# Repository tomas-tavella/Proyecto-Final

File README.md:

# Proyecto-Final
Repositorio para todo lo que respecta al proyecto final de pilas de hidrogeno

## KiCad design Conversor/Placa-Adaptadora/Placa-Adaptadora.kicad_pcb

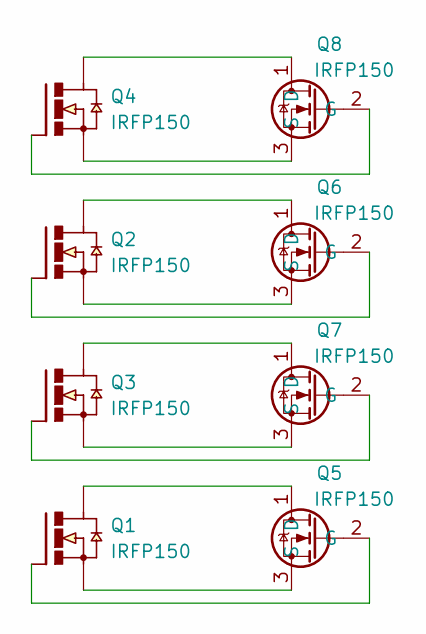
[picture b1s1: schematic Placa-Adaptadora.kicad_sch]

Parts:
Q1, Q2, Q3, Q4: IRFP150; TO247BV
Q5, Q6, Q7, Q8: IRFP150; TO-247-3_Vertical

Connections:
unnamed: Q2.D, Q6.1 (D)
unnamed: Q2.S, Q6.3 (S)
unnamed: Q4.D, Q8.1 (D)
unnamed: Q4.S, Q8.3 (S)
unnamed: Q1.D, Q5.1 (D)
unnamed: Q1.G, Q5.2 (G)
unnamed: Q1.S, Q5.3 (S)
unnamed: Q2.G, Q6.2 (G)
unnamed: Q3.D, Q7.1 (D)
unnamed: Q3.G, Q7.2 (G)
unnamed: Q3.S, Q7.3 (S)
unnamed: Q4.G, Q8.2 (G)

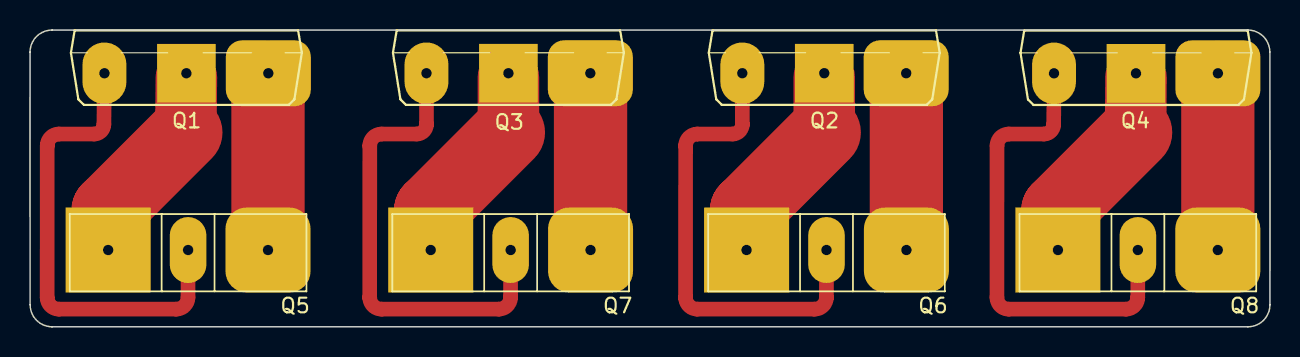
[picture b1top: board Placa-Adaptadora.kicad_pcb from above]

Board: 2 copper layers, 84.6 x 20.2 mm, 8 parts (0 on the bottom side), 12 nets.

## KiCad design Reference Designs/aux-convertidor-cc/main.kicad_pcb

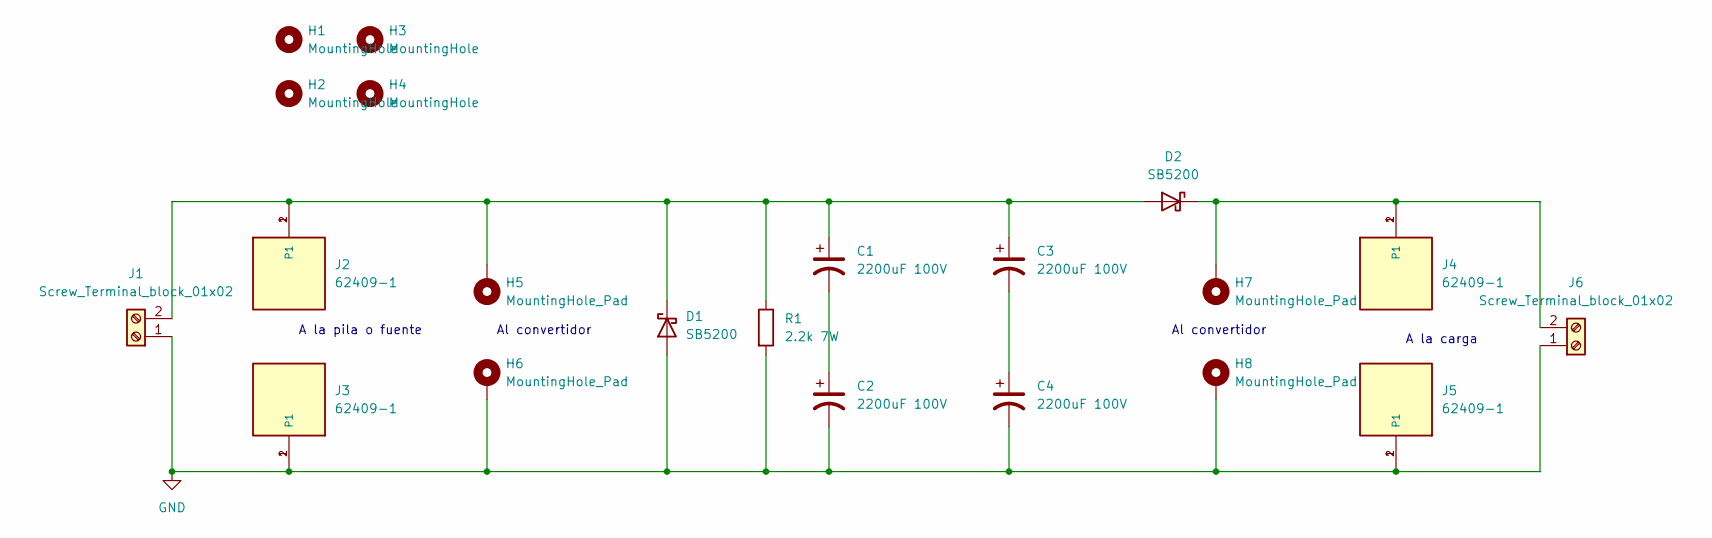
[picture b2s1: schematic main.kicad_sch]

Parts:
C1, C2, C3, C4: 2200uF 100V; CP_Radial_D25.0mm_P10.00mm_SnapIn
D1, D2: SB5200; D_DO-27_P15.24mm_Horizontal
H1, H2, H3, H4: MountingHole; MountingHole_3.2mm_M3
H5, H6, H7, H8: MountingHole_Pad; MountingHole_3.2mm_M3_Pad
J1, J6: Screw_Terminal_block_01x02; Degson_Screw_Terminal_block_01x02
J2, J3, J4, J5: 62409-1; TE_62409-1
R1: 2.2k 7W; R_Axial_Power_L38.0mm_W9.0mm_P40.64mm

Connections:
GND: C2.2, C4.2, D1.2 (A), H6.1, H8.1, J1.1, J3.1, J3.2 (P1), J5.1, J5.2 (P1), J6.1, R1.2
unnamed: C1.1, C3.1, D1.1 (K), D2.2 (A), H5.1, J1.2, J2.1, J2.2 (P1), R1.1
unnamed: C1.2, C2.1
unnamed: C3.2, C4.1
unnamed: D2.1 (K), H7.1, J4.1, J4.2 (P1), J6.2

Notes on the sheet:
Al convertidor
A la pila o fuente
A la carga

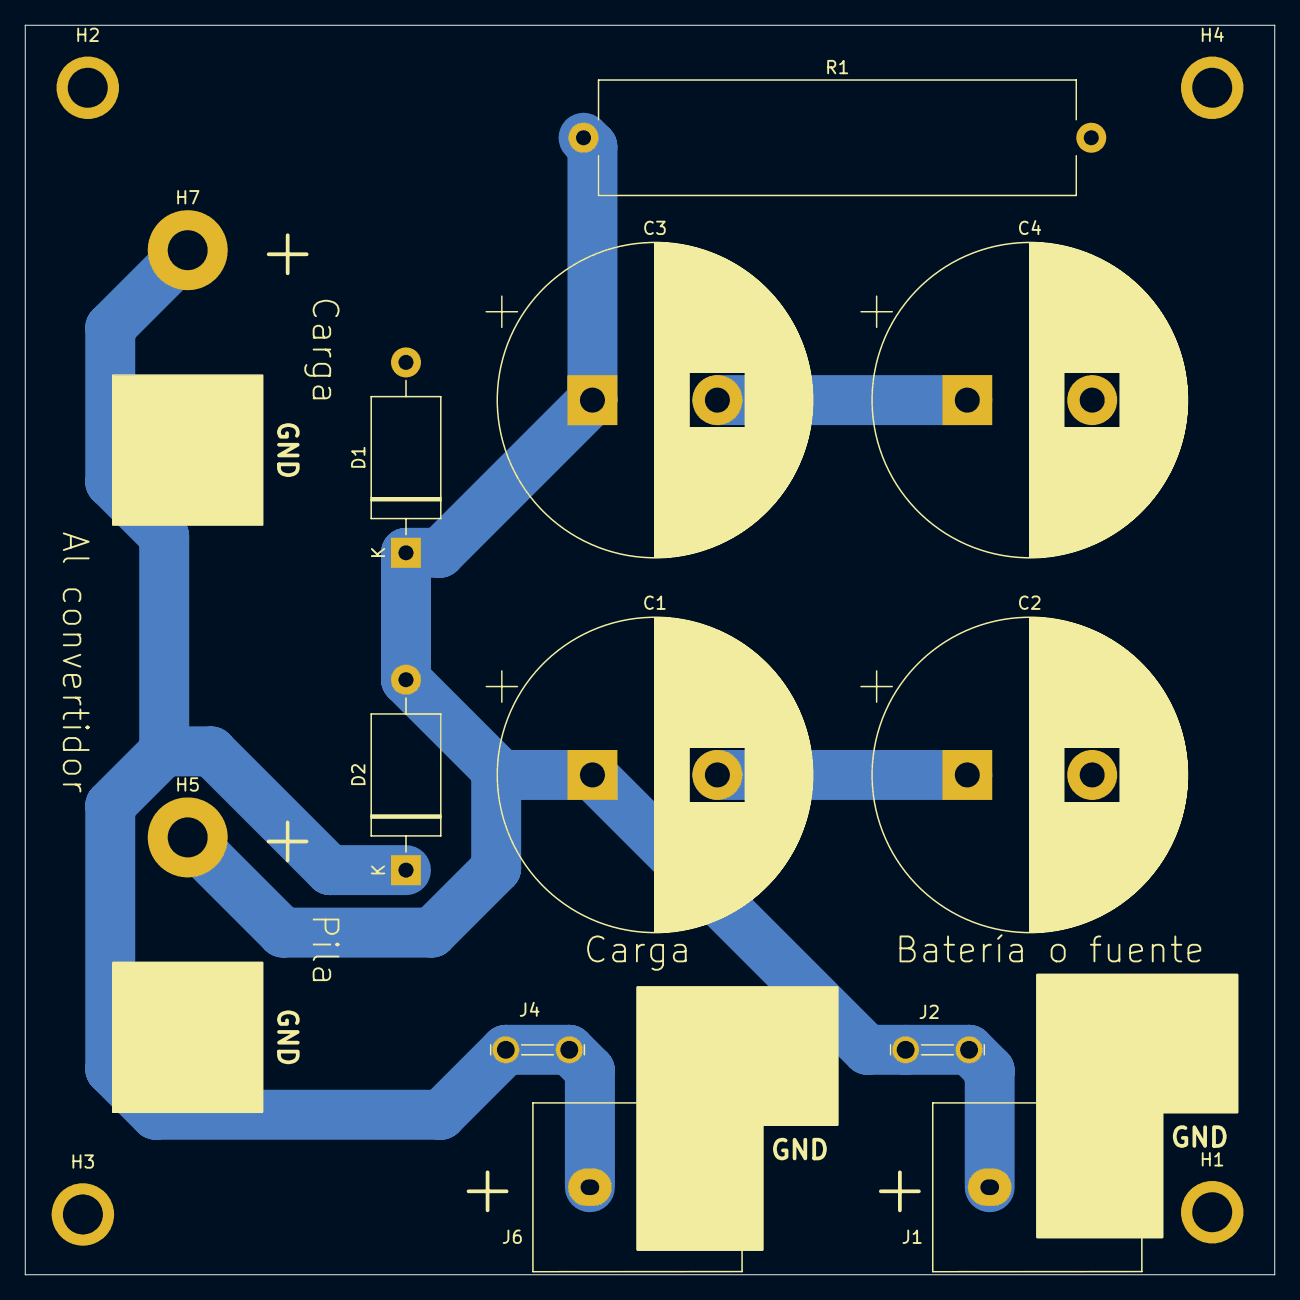
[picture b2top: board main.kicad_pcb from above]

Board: 2 copper layers, 100.0 x 100.0 mm, 21 parts (0 on the bottom side), 5 nets.

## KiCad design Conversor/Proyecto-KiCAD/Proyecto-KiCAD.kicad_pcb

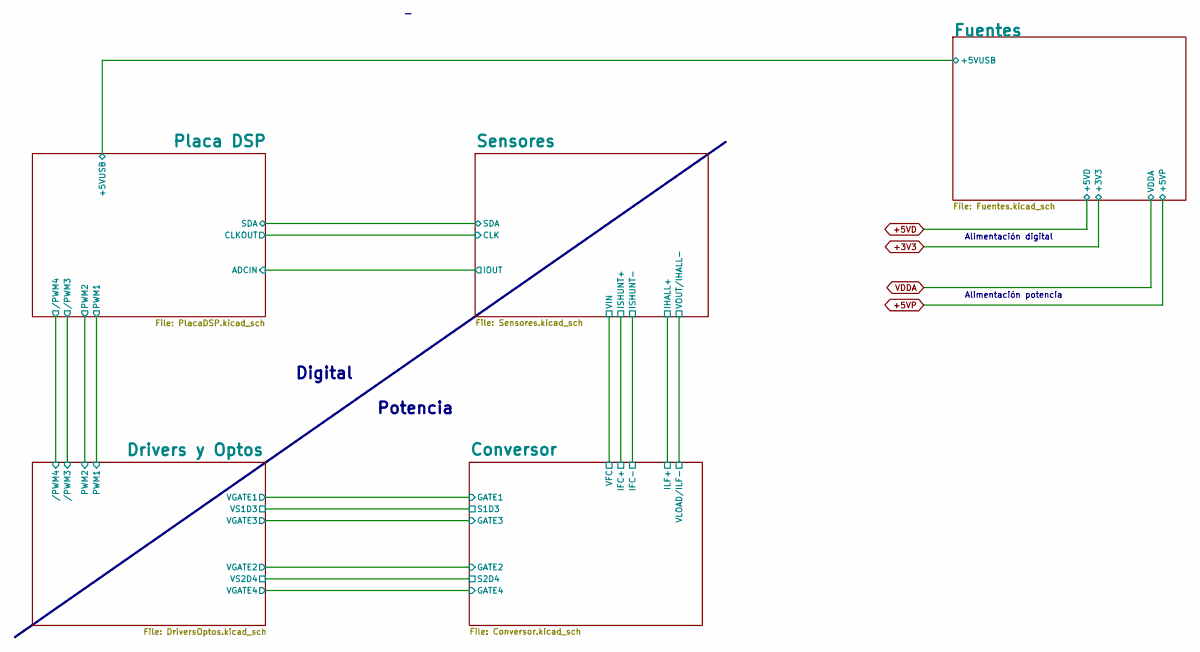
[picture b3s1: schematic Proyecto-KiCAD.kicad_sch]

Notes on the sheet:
Digital
Alimentación potencia
Potencia
Alimentación digital

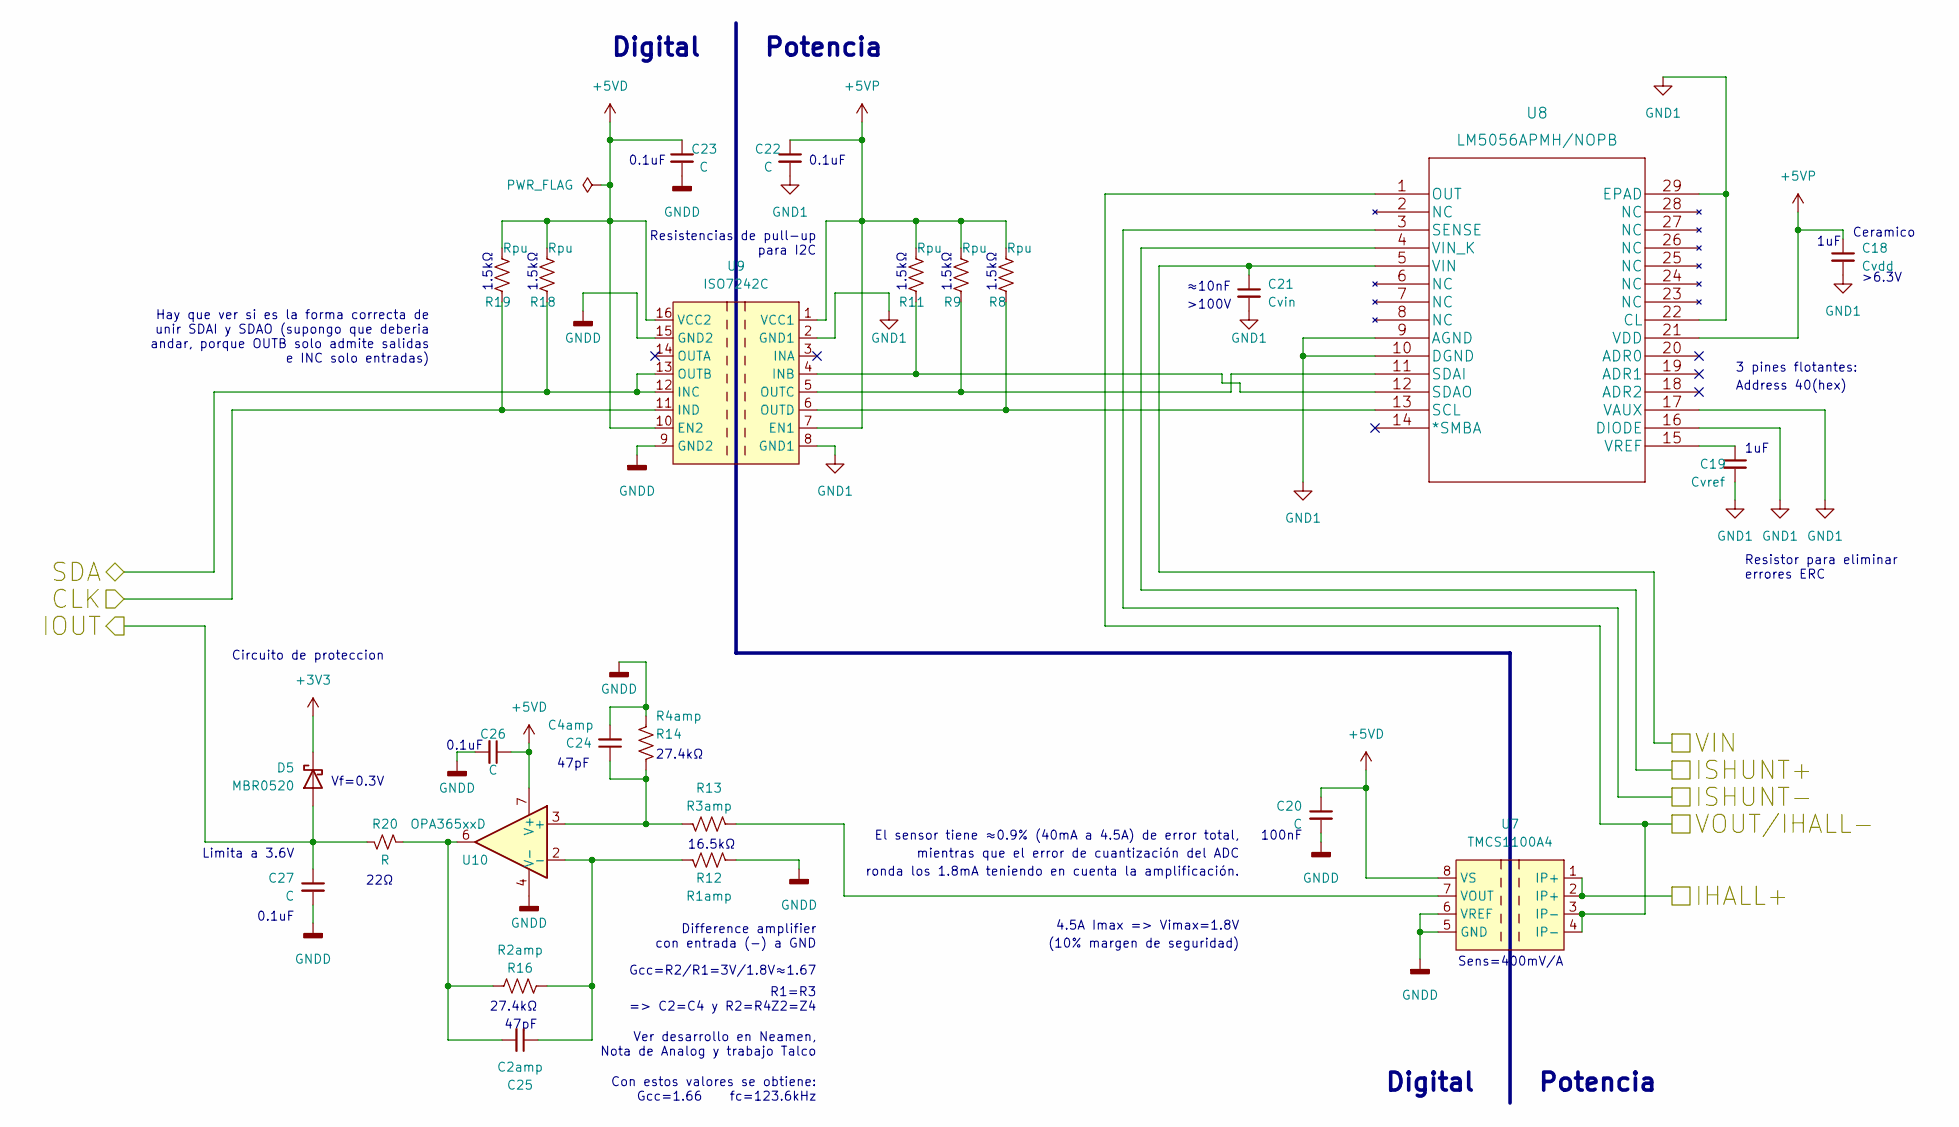
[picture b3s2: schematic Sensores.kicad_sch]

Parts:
C18: Cvdd; C_1206_3216Metric_Pad1.33x1.80mm_HandSolder
C19: Cvref; C_1206_3216Metric_Pad1.33x1.80mm_HandSolder
C20, C22, C23, C26, C27: C; C_1206_3216Metric_Pad1.33x1.80mm_HandSolder
C21: Cvin; C_1206_3216Metric_Pad1.33x1.80mm_HandSolder
C24: C4amp; C_1206_3216Metric_Pad1.33x1.80mm_HandSolder
C25: C2amp; C_1206_3216Metric_Pad1.33x1.80mm_HandSolder
D5: MBR0520; D_SOD-123
R8, R9, R11, R18, R19: Rpu; R_1206_3216Metric_Pad1.30x1.75mm_HandSolder
R12: R1amp; R_1206_3216Metric_Pad1.30x1.75mm_HandSolder
R13: R3amp; R_1206_3216Metric_Pad1.30x1.75mm_HandSolder
R14: R4amp; R_1206_3216Metric_Pad1.30x1.75mm_HandSolder
R16: R2amp; R_1206_3216Metric_Pad1.30x1.75mm_HandSolder
R20: R; R_1206_3216Metric_Pad1.30x1.75mm_HandSolder
U7: TMCS1100A4; SOIC-8_3.9x4.9mm_P1.27mm
U8: LM5056APMH/NOPB; HTSSOP-28-1EP_4.4x9.7mm_P0.65mm_EP2.85x5.4mm
U9: ISO7242C; SOIC-16W_7.5x10.3mm_P1.27mm
U10: OPA365xxD; SOIC-8_3.9x4.9mm_P1.27mm

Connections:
+3V3: D5.1 (K); also elsewhere on the board
+5VD: C20.1, C23.1, C26.1, R18.1, R19.1, U7.8 (VS), U9.10 (EN2), U9.16 (VCC2), U10.7 (V+); also elsewhere on the board
+5VP: C18.1, C22.1, R8.1, R9.1, R11.1, U8.21 (VDD), U9.1 (VCC1), U9.7 (EN1); also elsewhere on the board
/Conversor/IFC+: C21.1, U8.4 (VIN_K), U8.5 (VIN); also elsewhere on the board
/Conversor/IFC-: U8.3 (SENSE); also elsewhere on the board
/Conversor/ILF+: U7.1 (IP+), U7.2 (IP+); also elsewhere on the board
/Conversor/VLOAD/ILF-: U7.3 (IP-), U7.4 (IP-), U8.1 (OUT); also elsewhere on the board
/Placa DSP/Socket Interfaces/ADCIN-A0: C27.1, D5.2 (A), R20.2; also elsewhere on the board
/Placa DSP/Socket Interfaces/I2CSCL: R19.2, U9.11 (IND); also elsewhere on the board
/Placa DSP/Socket Interfaces/I2CSDA: R18.2, U9.12 (INC), U9.13 (OUTB); also elsewhere on the board
GND1: C18.2, C19.2, C21.2, C22.2, U8.9 (AGND), U8.10 (DGND), U8.16 (DIODE), U8.17 (VAUX), U8.22 (CL), U8.29 (EPAD), U9.2 (GND1), U9.8 (GND1); also elsewhere on the board
GNDD: C20.2, C23.2, C24.2, C26.2, C27.2, R12.1, R14.2, U7.5 (GND), U7.6 (VREF), U9.9 (GND2), U9.15 (GND2), U10.4 (V-); also elsewhere on the board
unnamed: C19.1, U8.15 (VREF)
unnamed: C24.1, R13.2, R14.1, U10.3 (+)
unnamed: C25.1, R12.2, R16.1, U10.2 (-)
unnamed: C25.2, R16.2, R20.1, U10.6
unnamed: R8.2, U8.13 (SCL), U9.6 (OUTD)
unnamed: R9.2, U8.11 (SDAI), U9.5 (OUTC)
unnamed: R11.2, U8.12 (SDAO), U9.4 (INB)
unnamed: R13.1, U7.7 (VOUT)

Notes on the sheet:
Sens=400mV/A
mientras que el error de cuantización del ADC
Ver desarrollo en Neamen, Nota de Analog y trabajo Talco
Gcc=R2/R1=3V/1.8V≈1.67
3 pines flotantes:
1.5kΩ
≈10nF
Vf=0.3V
R1=R3 Z2=Z4
1uF
Con estos valores se obtiene: Gcc=1.66 fc=123.6kHz
16.5kΩ
Limita a 3.6V
0.1uF
>6.3V
22Ω
100nF
=> C2=C4 y R2=R4
Digital
Resistor para eliminar errores ERC
Hay que ver si es la forma correcta de unir SDAI y SDAO (supongo que deberia andar, porque OUTB solo admite salidas e INC solo entradas)
(10% margen de seguridad)
Address 40(hex)
Potencia
Ceramico
47pF
27.4kΩ
Circuito de proteccion
Resistencias de pull-up para I2C
>100V
Difference amplifier con entrada (-) a GND
4.5A Imax => Vimax=1.8V
El sensor tiene ≈0.9% (40mA a 4.5A) de error total,
ronda los 1.8mA teniendo en cuenta la amplificación.

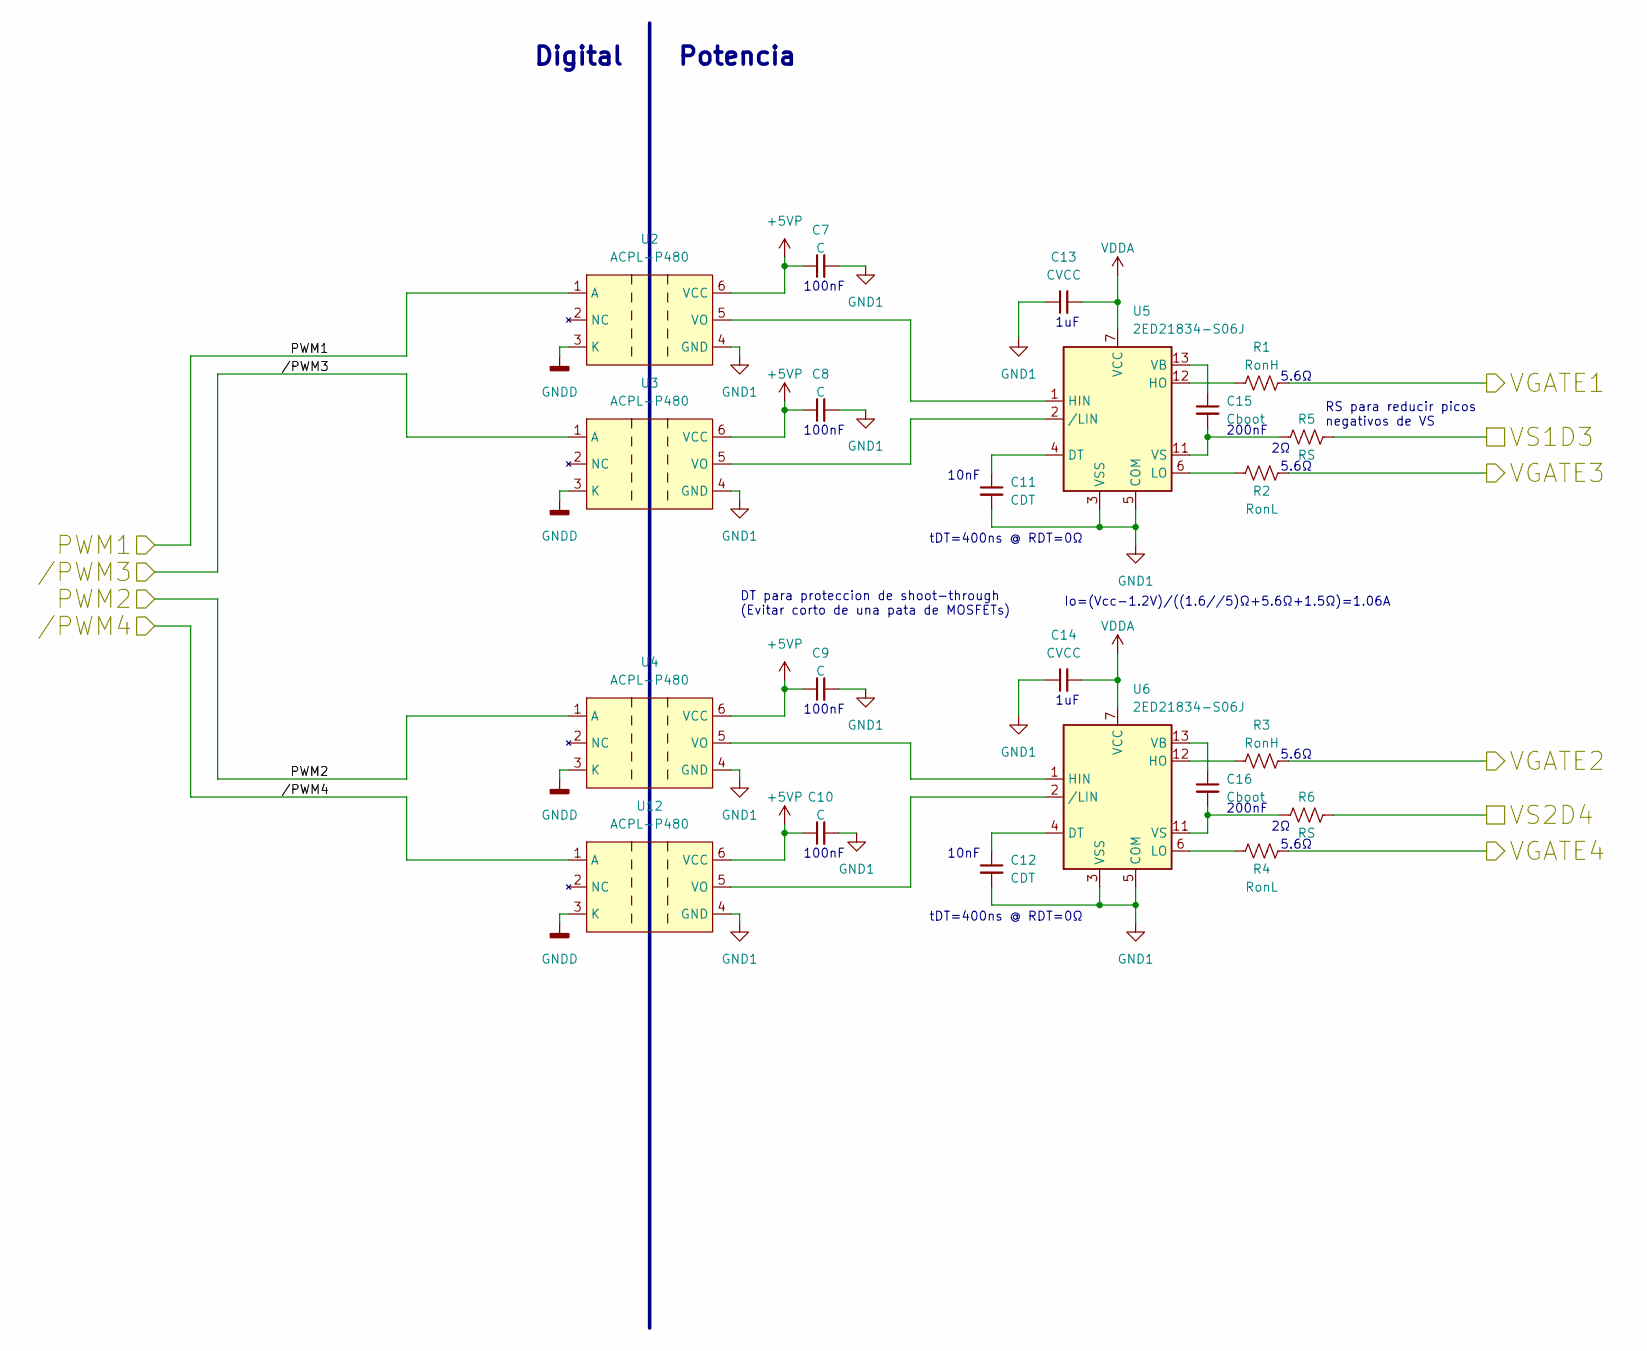
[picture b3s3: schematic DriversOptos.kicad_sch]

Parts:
C7, C8, C9, C10: C; C_1206_3216Metric_Pad1.33x1.80mm_HandSolder
C11, C12: CDT; C_1206_3216Metric_Pad1.33x1.80mm_HandSolder
C13, C14: CVCC; C_1206_3216Metric_Pad1.33x1.80mm_HandSolder
C15, C16: Cboot; C_1206_3216Metric_Pad1.33x1.80mm_HandSolder
R1, R3: RonH; R_1206_3216Metric_Pad1.30x1.75mm_HandSolder
R2, R4: RonL; R_1206_3216Metric_Pad1.30x1.75mm_HandSolder
R5, R6: RS; R_1206_3216Metric_Pad1.30x1.75mm_HandSolder
U2, U3, U4, U12: ACPL-P480; SSO-6_6.8x4.6mm_P1.27mm_Clearance7mm
U5, U6: 2ED21834-S06J; SO-14_3.9x8.65mm_P1.27mm

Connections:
+5VP: C7.1, C8.1, C9.1, C10.1, U2.6 (VCC), U3.6 (VCC), U4.6 (VCC), U12.6 (VCC); also elsewhere on the board
/Conversor/GATE1: R1.2; also elsewhere on the board
/Conversor/GATE2: R3.2; also elsewhere on the board
/Conversor/GATE3: R2.2; also elsewhere on the board
/Conversor/GATE4: R4.2; also elsewhere on the board
/Conversor/S1D3: R5.2; also elsewhere on the board
/Conversor/S2D4: R6.2; also elsewhere on the board
/Drivers y Optos/PWM1: U2.1 (A); also elsewhere on the board
/Drivers y Optos/PWM2: U4.1 (A); also elsewhere on the board
/Drivers y Optos//PWM3: U3.1 (A); also elsewhere on the board
/Drivers y Optos//PWM4: U12.1 (A); also elsewhere on the board
GND1: C7.2, C8.2, C9.2, C10.2, C11.2, C12.2, C13.1, C14.1, U2.4 (GND), U3.4 (GND), U4.4 (GND), U5.3 (VSS), U5.5 (COM), U6.3 (VSS), U6.5 (COM), U12.4 (GND); also elsewhere on the board
GNDD: U2.3 (K), U3.3 (K), U4.3 (K), U12.3 (K); also elsewhere on the board
unnamed: C11.1, U5.4 (DT)
unnamed: C12.1, U6.4 (DT)
unnamed: C15.1, U5.13 (VB)
unnamed: C15.2, R5.1, U5.11 (VS)
unnamed: C16.1, U6.13 (VB)
unnamed: C16.2, R6.1, U6.11 (VS)
unnamed: R1.1, U5.12 (HO)
unnamed: R2.1, U5.6 (LO)
unnamed: R3.1, U6.12 (HO)
unnamed: R4.1, U6.6 (LO)
unnamed: U2.5 (VO), U5.1 (HIN)
unnamed: U3.5 (VO), U5.2 (/LIN)
unnamed: U4.5 (VO), U6.1 (HIN)
unnamed: U6.2 (/LIN), U12.5 (VO)
VDDA: C13.2, C14.2, U5.7 (VCC), U6.7 (VCC); also elsewhere on the board

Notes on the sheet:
Io=(Vcc-1.2V)/((1.6//5)Ω+5.6Ω+1.5Ω)=1.06A
100nF
200nF
5.6Ω
RS para reducir picos negativos de VS
1uF
DT para proteccion de shoot-through (Evitar corto de una pata de MOSFETs)
tDT=400ns @ RDT=0Ω
Digital
Potencia
10nF

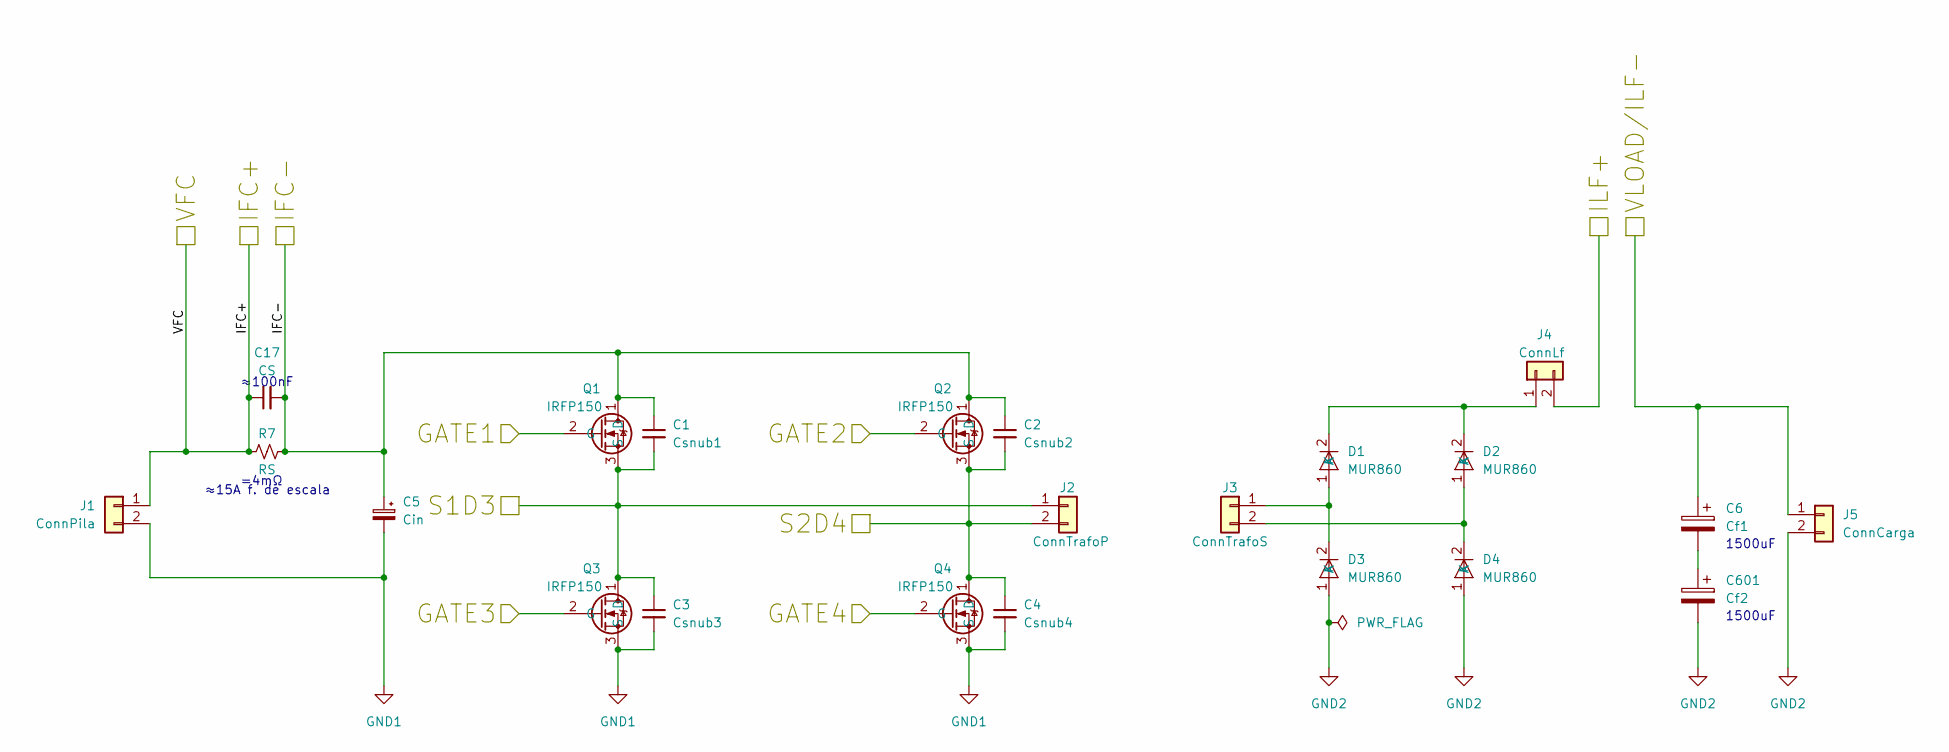
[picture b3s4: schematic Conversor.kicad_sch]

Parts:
C1: Csnub1; C_1206_3216Metric_Pad1.33x1.80mm_HandSolder
C2: Csnub2; C_1206_3216Metric_Pad1.33x1.80mm_HandSolder
C3: Csnub3; C_1206_3216Metric_Pad1.33x1.80mm_HandSolder
C4: Csnub4; C_1206_3216Metric_Pad1.33x1.80mm_HandSolder
C5: Cin; CP_Radial_D12.5mm_P5.00mm
C6: Cf1; CP_Radial_D18.0mm_P7.50mm
C17: CS; C_1206_3216Metric_Pad1.33x1.80mm_HandSolder
C601: Cf2; CP_Radial_D18.0mm_P7.50mm
D1, D2, D3, D4: MUR860; TO-220F-2_Vertical
J1: ConnPila; TerminalBlock_Wuerth_691311400102_P7.62mm
J2: ConnTrafoP; TerminalBlock_Wuerth_691311400102_P7.62mm
J3: ConnTrafoS; TerminalBlock_Wuerth_691311400102_P7.62mm
J4: ConnLf; TerminalBlock_Wuerth_691311400102_P7.62mm
J5: ConnCarga; TerminalBlock_Wuerth_691311400102_P7.62mm
Q1, Q2, Q3, Q4: IRFP150; TO-247-3_Vertical
R7: RS; R_2512_6332Metric_Pad1.40x3.35mm_HandSolder

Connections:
/Conversor/GATE1: Q1.2 (G); also elsewhere on the board
/Conversor/GATE2: Q2.2 (G); also elsewhere on the board
/Conversor/GATE3: Q3.2 (G); also elsewhere on the board
/Conversor/GATE4: Q4.2 (G); also elsewhere on the board
/Conversor/IFC+: C17.1, J1.1, R7.1; also elsewhere on the board
/Conversor/IFC-: C1.1, C2.1, C5.1, C17.2, Q1.1 (D), Q2.1 (D), R7.2; also elsewhere on the board
/Conversor/ILF+: J4.2; also elsewhere on the board
/Conversor/S1D3: C1.2, C3.1, J2.1, Q1.3 (S), Q3.1 (D); also elsewhere on the board
/Conversor/S2D4: C2.2, C4.1, J2.2, Q2.3 (S), Q4.1 (D); also elsewhere on the board
/Conversor/VLOAD/ILF-: C6.1, J5.1; also elsewhere on the board
GND1: C3.2, C4.2, C5.2, J1.2, Q3.3 (S), Q4.3 (S); also elsewhere on the board
GND2: C601.2, D3.1 (A), D4.1 (A), J5.2; also elsewhere on the board
unnamed: C6.2, C601.1
unnamed: D1.1 (A), D3.2 (K), J3.1
unnamed: D1.2 (K), D2.2 (K), J4.1
unnamed: D2.1 (A), D4.2 (K), J3.2

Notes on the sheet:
=4mΩ
1500uF
≈15A f. de escala
≈100nF

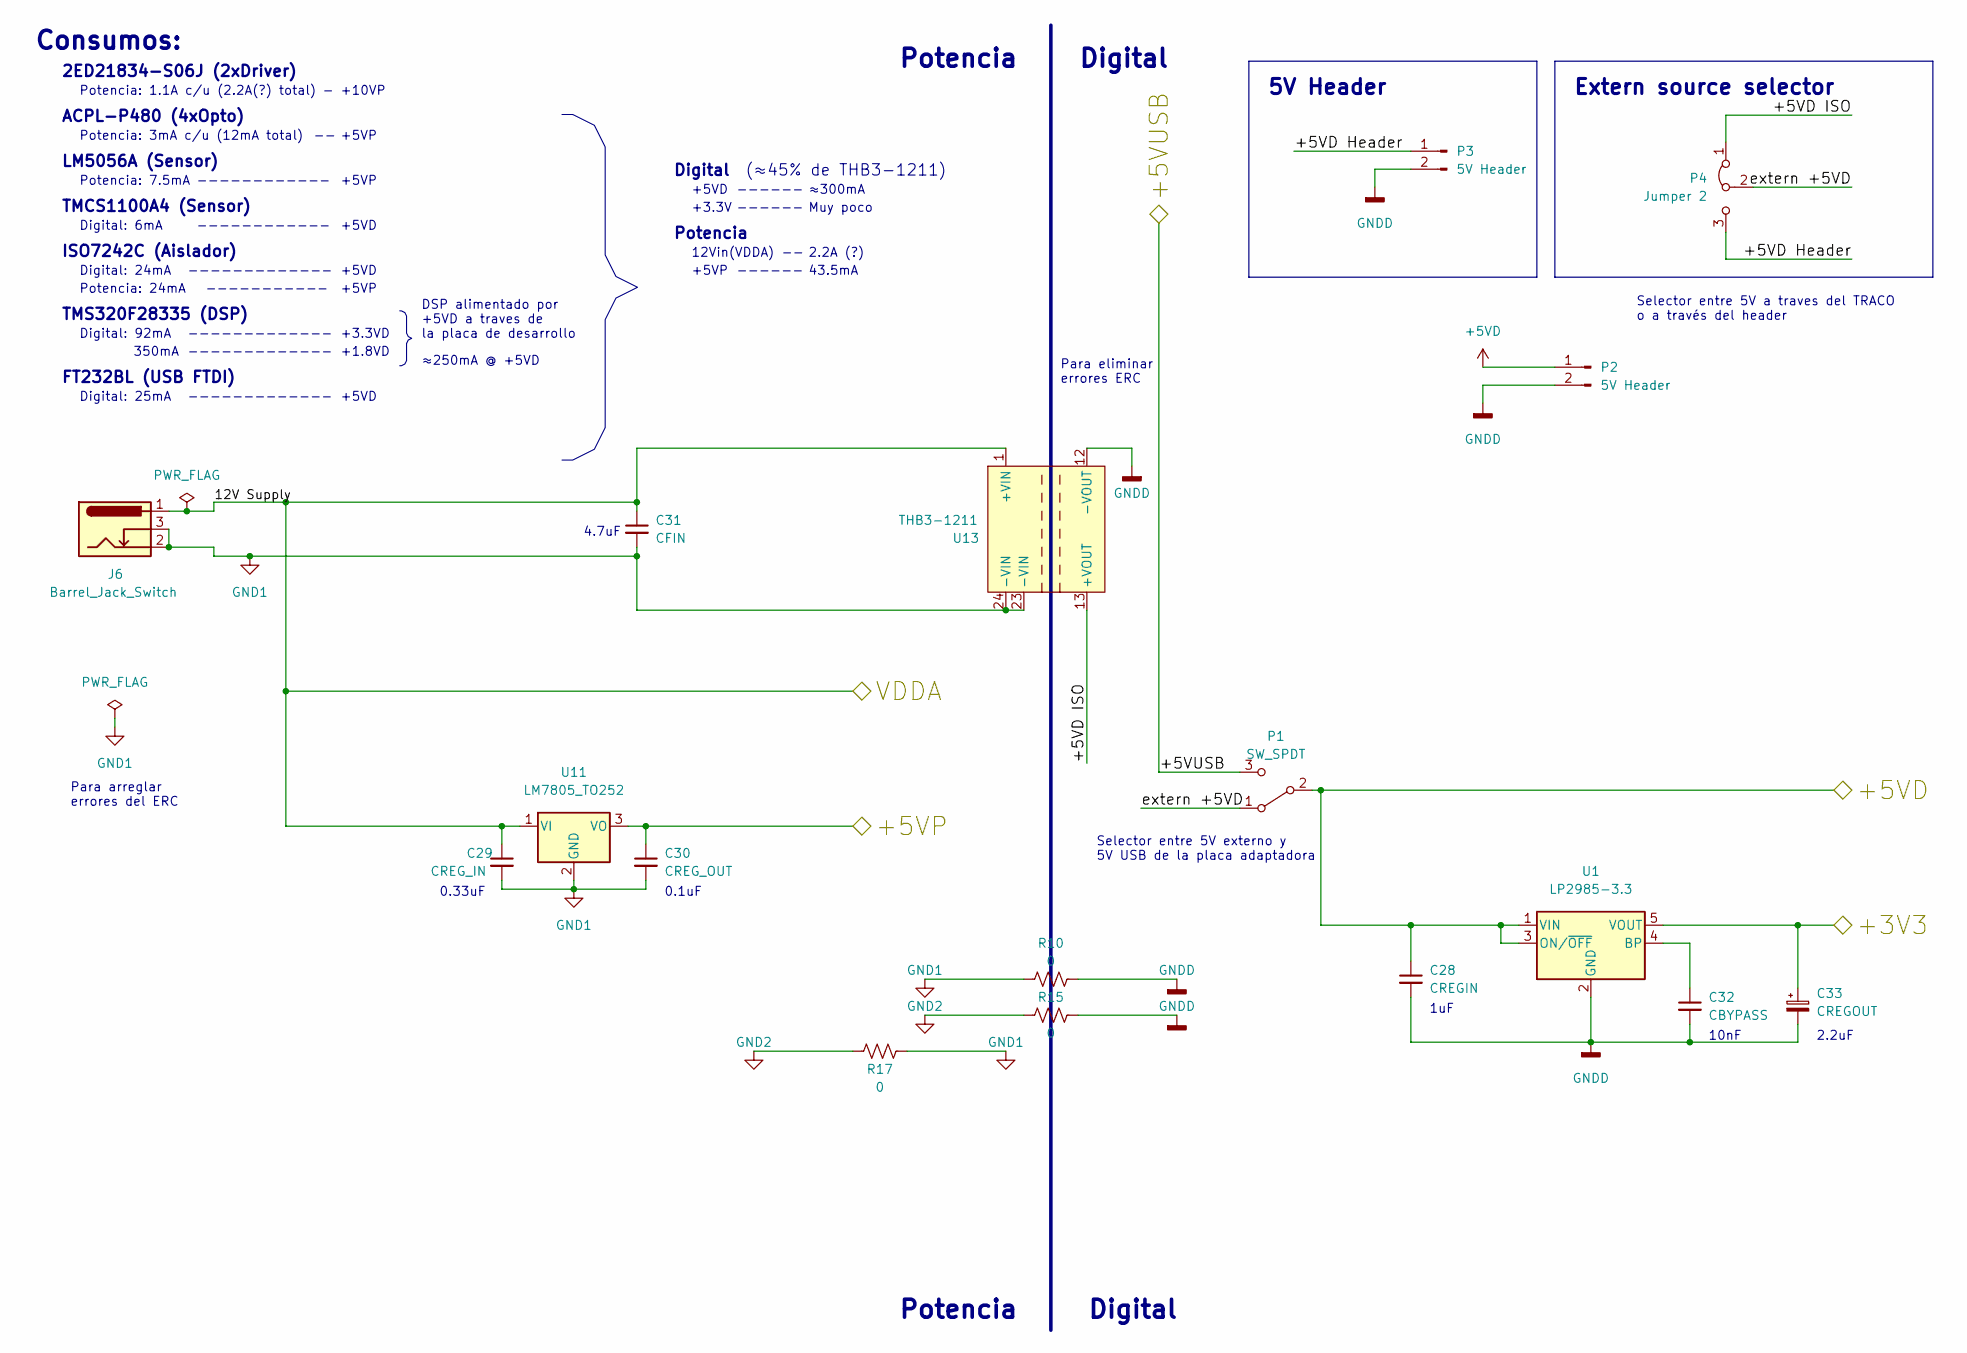
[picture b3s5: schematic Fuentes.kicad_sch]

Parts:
C28: CREGIN; C_1206_3216Metric_Pad1.33x1.80mm_HandSolder
C29: CREG_IN; C_1206_3216Metric_Pad1.33x1.80mm_HandSolder
C30: CREG_OUT; C_1206_3216Metric_Pad1.33x1.80mm_HandSolder
C31: CFIN; C_1206_3216Metric_Pad1.33x1.80mm_HandSolder
C32: CBYPASS; C_1206_3216Metric_Pad1.33x1.80mm_HandSolder
C33: CREGOUT; C_1206_3216Metric_Pad1.33x1.80mm_HandSolder
J6: Barrel_Jack_Switch; BarrelJack_GCT_DCJ200-10-A_Horizontal
P1: SW_SPDT; PinHeader_1x03_P2.54mm_Vertical
P2, P3: 5V Header; PinHeader_1x02_P2.54mm_Vertical
P4: Jumper 2; PinHeader_1x03_P2.54mm_Vertical
R10, R15, R17: 0; R_1206_3216Metric_Pad1.30x1.75mm_HandSolder
U1: LP2985-3.3; SOT-23-5
U11: LM7805_TO252; TO-252-2
U13: THB3-1211; DIP-24_W15.24mm

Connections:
+3V3: C33.1, U1.5 (VOUT); also elsewhere on the board
+5VD: C28.1, P1.2 (B), P2.1, U1.1 (VIN), U1.3 (ON/~OFF); also elsewhere on the board
+5VP: C30.1, U11.3 (VO); also elsewhere on the board
/Fuentes/+5VD Header: P3.1, P4.3 (B)
/Fuentes/+5VD ISO: P4.1 (A), U13.13 (+VOUT)
/Fuentes/+5VUSB: P1.3 (C); also elsewhere on the board
/Fuentes/extern +5VD: P1.1 (A), P4.2 (C)
GND1: C29.2, C30.2, C31.2, J6.2, J6.3, R10.1, R17.2, U11.2 (GND), U13.23 (-VIN), U13.24 (-VIN); also elsewhere on the board
GND2: R15.1, R17.1; also elsewhere on the board
GNDD: C28.2, C32.2, C33.2, P2.2, P3.2, R10.2, R15.2, U1.2 (GND), U13.12 (-VOUT); also elsewhere on the board
unnamed: C32.1, U1.4 (BP)
VDDA: C29.1, C31.1, J6.1, U11.1 (VI), U13.1 (+VIN); also elsewhere on the board

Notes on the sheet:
350mA
+3.3V
Consumos:
Potencia: 7.5mA
Selector entre 5V externo y 5V USB de la placa adaptadora
Potencia: 3mA c/u (12mA total)
(?)
0.33uF
ISO7242C (Aislador)
Potencia: 1.1A c/u (2.2A(?) total)
Potencia
Selector entre 5V a traves del TRACO o a través del header
+5VD
Digital: 25mA
Digital
5V Header
+5VP
+10VP
TMS320F28335 (DSP)
Potencia: 24mA
≈300mA
-----------
12Vin(VDDA)
LM5056A (Sensor)
43.5mA
1uF
------------
------
ACPL-P480 (4xOpto)
Para eliminar errores ERC
Digital: 92mA
+1.8VD
TMCS1100A4 (Sensor)
Muy poco
Digital: 6mA
Extern source selector
-------------
≈250mA @ +5VD
2.2uF
2ED21834-S06J (2xDriver)

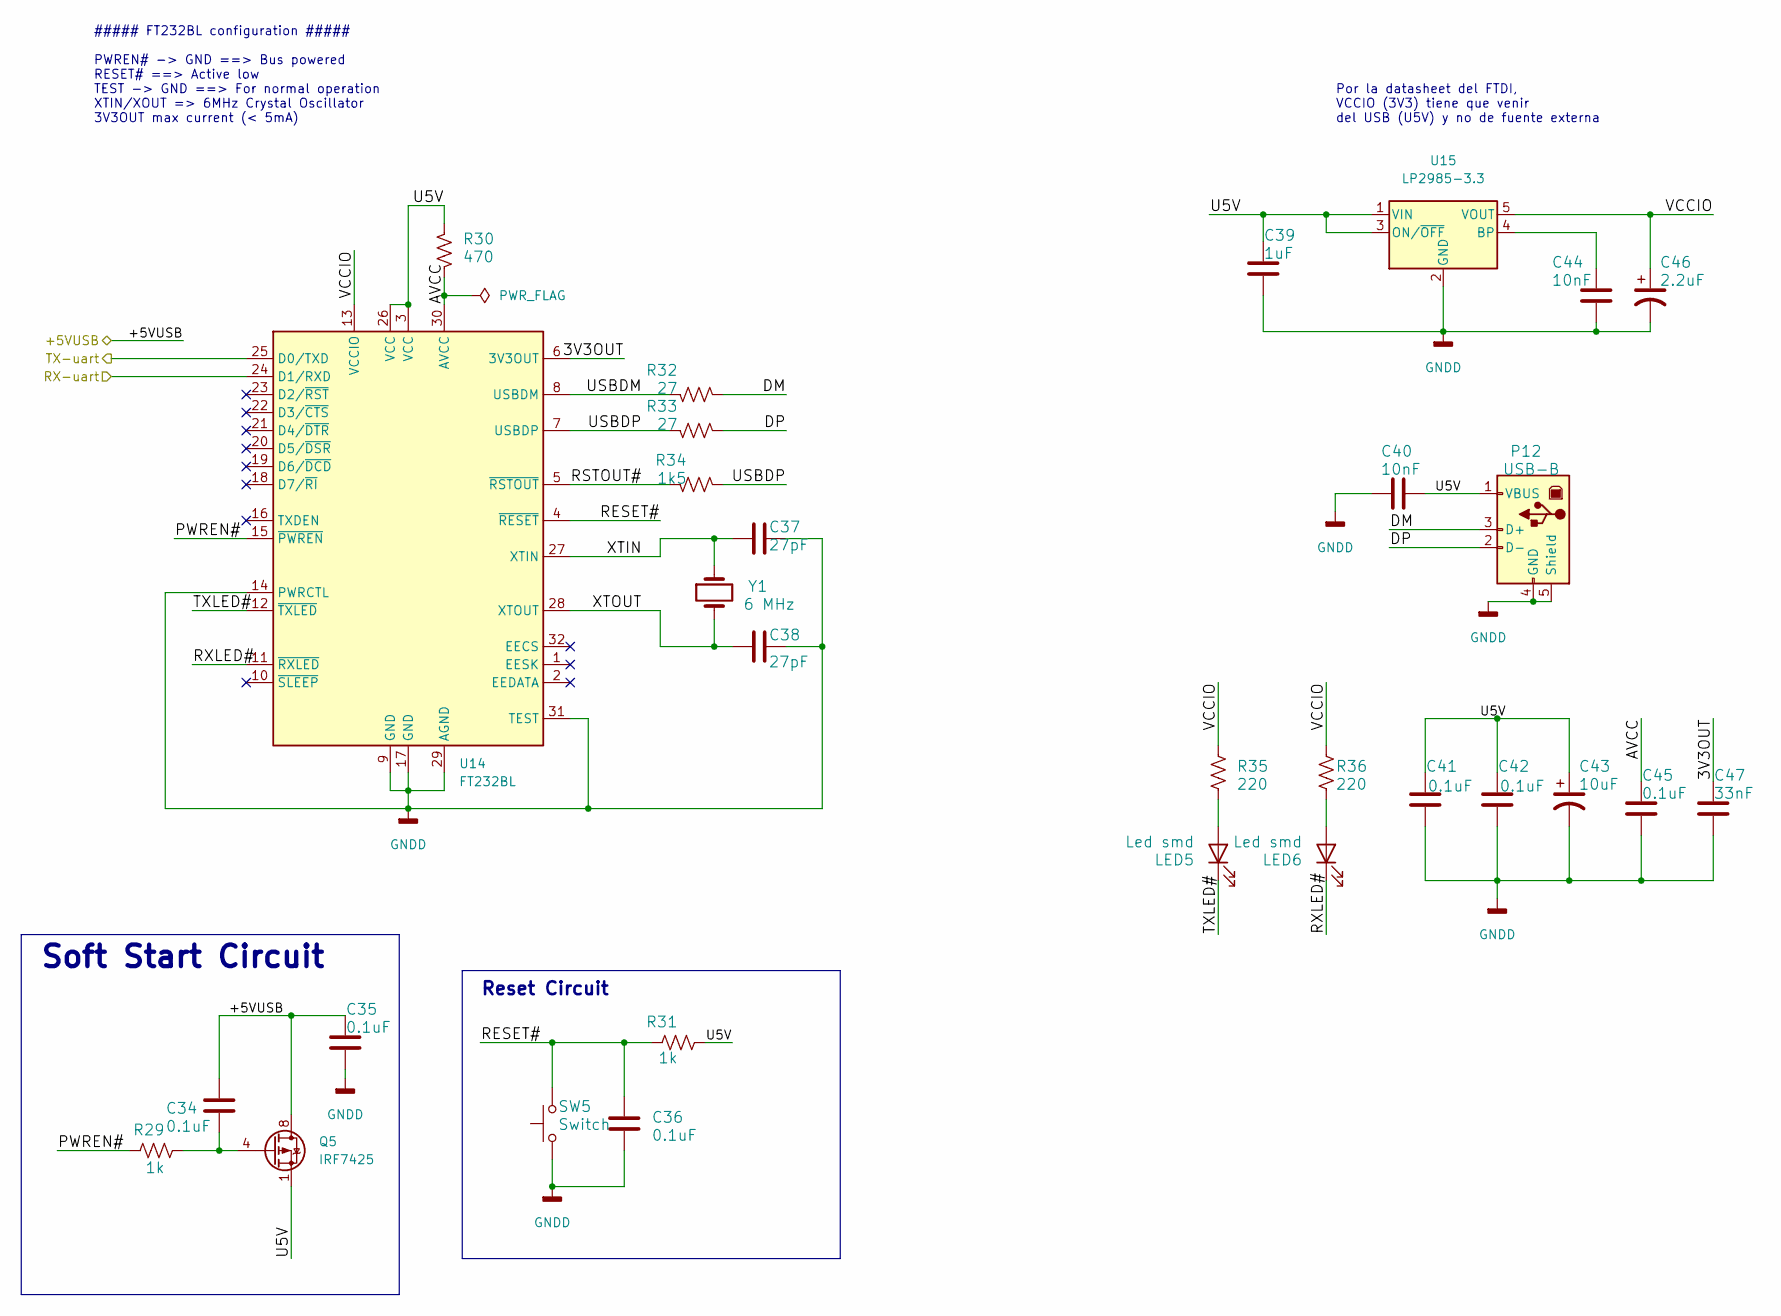
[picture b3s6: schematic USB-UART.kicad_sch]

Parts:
C34, C35, C36, C41, C42, C45: 0.1uF; C_1206_3216Metric_Pad1.33x1.80mm_HandSolder
C37, C38: 27pF; C_1206_3216Metric_Pad1.33x1.80mm_HandSolder
C39: 1uF; C_1206_3216Metric_Pad1.33x1.80mm_HandSolder
C40, C44: 10nF; C_1206_3216Metric_Pad1.33x1.80mm_HandSolder
C43: 10uF; CP_Radial_D4.0mm_P1.50mm
C46: 2.2uF; CP_Radial_D4.0mm_P2.00mm
C47: 33nF; C_1206_3216Metric_Pad1.33x1.80mm_HandSolder
LED5, LED6: Led smd; D_1206_3216Metric_Pad1.42x1.75mm_HandSolder
P12: USB-B; USB_B_Lumberg_2411_02_Horizontal
Q5: IRF7425; SOIC-8_3.9x4.9mm_P1.27mm
R29, R31: 1k; R_1206_3216Metric_Pad1.30x1.75mm_HandSolder
R30: 470; R_1206_3216Metric_Pad1.30x1.75mm_HandSolder
R32, R33: 27; R_1206_3216Metric_Pad1.30x1.75mm_HandSolder
R34: 1k5; R_1206_3216Metric_Pad1.30x1.75mm_HandSolder
R35, R36: 220; R_1206_3216Metric_Pad1.30x1.75mm_HandSolder
SW5: Switch; SW_PUSH_6mm
U14: FT232BL; LQFP-32_7x7mm_P0.8mm
U15: LP2985-3.3; SOT-23-5
Y1: 6 MHz; Crystal_HC18-U_Vertical

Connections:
/Fuentes/+5VUSB: C34.1, C35.1, Q5.5 (D), Q5.6 (D), Q5.7 (D), Q5.8 (D); also elsewhere on the board
/Placa DSP/Socket Interfaces/SCI-RX: U14.24 (D1/RXD); also elsewhere on the board
/Placa DSP/Socket Interfaces/SCI-TX: U14.25 (D0/TXD); also elsewhere on the board
/Placa DSP/USB-UART/3V3OUT: C47.2, U14.6 (3V3OUT)
/Placa DSP/USB-UART/AVCC: C45.2, R30.1, U14.30 (AVCC)
/Placa DSP/USB-UART/DM: P12.3 (D+), R32.1
/Placa DSP/USB-UART/DP: P12.2 (D-), R33.1
/Placa DSP/USB-UART/PWREN#: R29.1, U14.15 (~PWREN)
/Placa DSP/USB-UART/RESET#: C36.1, R31.1, SW5.2, U14.4 (~RESET)
/Placa DSP/USB-UART/RSTOUT#: R34.2, U14.5 (~RSTOUT)
/Placa DSP/USB-UART/RXLED#: LED6.1 (K), U14.11 (~RXLED)
/Placa DSP/USB-UART/TXLED#: LED5.1 (K), U14.12 (~TXLED)
/Placa DSP/USB-UART/U5V: C39.1, C40.2, C41.2, C42.2, C43.1, P12.1 (VBUS), Q5.1 (S), Q5.2 (S), Q5.3 (S), R30.2, R31.2, U14.3 (VCC), U14.26 (VCC), U15.1 (VIN), U15.3 (ON/~OFF)
/Placa DSP/USB-UART/USBDM: R32.2, U14.8 (USBDM)
/Placa DSP/USB-UART/USBDP: R33.2, R34.1, U14.7 (USBDP)
/Placa DSP/USB-UART/VCCIO: C46.1, R35.1, R36.1, U14.13 (VCCIO), U15.5 (VOUT)
/Placa DSP/USB-UART/XTIN: C37.1, U14.27 (XTIN), Y1.1
/Placa DSP/USB-UART/XTOUT: C38.1, U14.28 (XTOUT), Y1.2
GNDD: C35.2, C36.2, C37.2, C38.2, C39.2, C40.1, C41.1, C42.1, C43.2, C44.2, C45.1, C46.2, C47.1, P12.4 (GND), P12.5 (Shield), SW5.1, U14.9 (GND), U14.14 (PWRCTL), U14.17 (GND), U14.29 (AGND), U14.31 (TEST), U15.2 (GND); also elsewhere on the board
unnamed: C34.2, Q5.4 (G), R29.2
unnamed: C44.1, U15.4 (BP)
unnamed: LED5.2 (A), R35.2
unnamed: LED6.2 (A), R36.2

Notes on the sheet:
Por la datasheet del FTDI, VCCIO (3V3) tiene que venir del USB (U5V) y no de fuente externa
Soft Start Circuit
##### FT232BL configuration ##### PWREN# -> GND ==> Bus powered RESET# ==> Active low TEST -> GND ==> For normal operation XTIN/XOUT => 6MHz Crystal Oscillator 3V3OUT max current (< 5mA)
Reset Circuit
